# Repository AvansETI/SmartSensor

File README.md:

# SmartSensor
Author: _Maurice Snoeren (Lectoraat Smart Energy en Datascience & ICT)_

De SmartSensor is een resultaat van verschillende onderzoeken sinds 2018. Focus is gegeven aan laag vermogen, controle over energiestromen en eenvoud. Deze SmartSensor wordt binnen onderzoek en onderwijs toegepast.

## Inleiding
Meten is weten! Het belang van meten en het verzamelen van informatie is wel bekend. Echter komt het vaak  voor dat data niet voorhanden is of dat de data van beschikbare systemen van onvoldoende kwaliteit is. Bestaande meetsystemen zijn vaak kostbaar en onvoldoende flexibel om de benodigde aanpassingen te maken die nodig zijn binnen de verschillende onderzoeken. De SmartSensor biedt een open platform, waarmee eenvoudig vele meetpunten in een omgeving geïnstalleerd kunnen worden. Het platform biedt de mogelijkheid eigen metingen toe te voegen. Uniek is dat het met de SmartSensor mogelijk wordt om met andere systemen te communiceren. Hierdoor wordt het mogelijk om tevens sturing aan te brengen. Een open platform dat binnen Avans Hogeschool wordt ingezet voor het onderzoek en onderwijs.

## SmartSensor specificatie
- Atmega324PB (Microcontroller)
- ATECC608B (Trusted Platform Module)
- Zigbee module (of nRF24L01)
- Real-time klok
- Omgevingslichtsensor (0lx t/m 167klx, 5mlx res.) 
- Temperatuursensor (±0.5˚C, -40 t/m 100˚C)
- Luchtvochtigheidssensor (±4.5 %RH)
- CO2 sensor (optional, eCO2, 400 t/m 8192ppm) 
- Interfaces: RS232 (3.3V), I2C en SPI
- Uitbreiden met header

## Werking
Alle SmartSensoren staan met elkaar in verbinding door middel van een Zigbee mesh-netwerk. Eén van de sensoren dient als een coördinator te dienen om de meet¬gegevens uit het systeem te krijgen. Via deze coördinator kunnen tevens commando’s naar de verschillende sensoren gestuurd worden om bijvoorbeeld een batterij op te laden of de verwarming in te stellen op 20 graden Celsius.

## Metingen bestaande gebouwen
Door op verschillende punten te meten, krijgt men inzicht in de energiehuishouding van het bestaande gebouw. In veel (oude) gebouwen zijn er geen of onvoldoende meetpunten aanwezig. Met behulp van de SmartSensor kunnen deze meetpunten eenvoudig worden toegevoegd. Doordat met gebouwsystemen communiceert kan worden, is het tevens mogelijk de gegevens van deze systemen te verzamelen en mee te nemen in de analyse.

## Verduurzaming gebouwen
Binnen gebouwen kan de SmartSensor meetpunten realiseren én communiceren met gebouwsystemen. Hierdoor wordt het mogelijk om een regelsysteem te realiseren waarbij het gebouw kan worden verduurzaamd. Gebouwsystemen worden dan aangestuurd op basis van verschillende metingen. Door de flexibiliteit van deze SmartSensor wordt het eenvoudig om verschillende strategieën en technieken te onderzoeken en ontdekken.

## Nieuwbouw
Nieuwe gebouwen worden vaak opgeleverd met veel sensoren en gebouwbeheersystemen. Meer meetpunten is vaak niet nodig. In dit geval is het mogelijk om de SmartSensor te gebruiken om het gebouw-beheersysteem te valideren. Door vele metingen aan te brengen krijgt men inzicht in de kwaliteit en effectiviteit van het bestaande systeem. Daarnaast is het mogelijk om met de SmartSensor eenvoudig extra meetpunten aan te brengen binnen het gebouw.

## Onderzoek
De SmartSensor speelt steeds meer een rol binnen de onderzoeken naar slimme duurzame energiesystemen, datascience vraagstukken en het zelfbewuste huis.

## Interesse
Interesse voor samenwerking? Neem contact met ons op!

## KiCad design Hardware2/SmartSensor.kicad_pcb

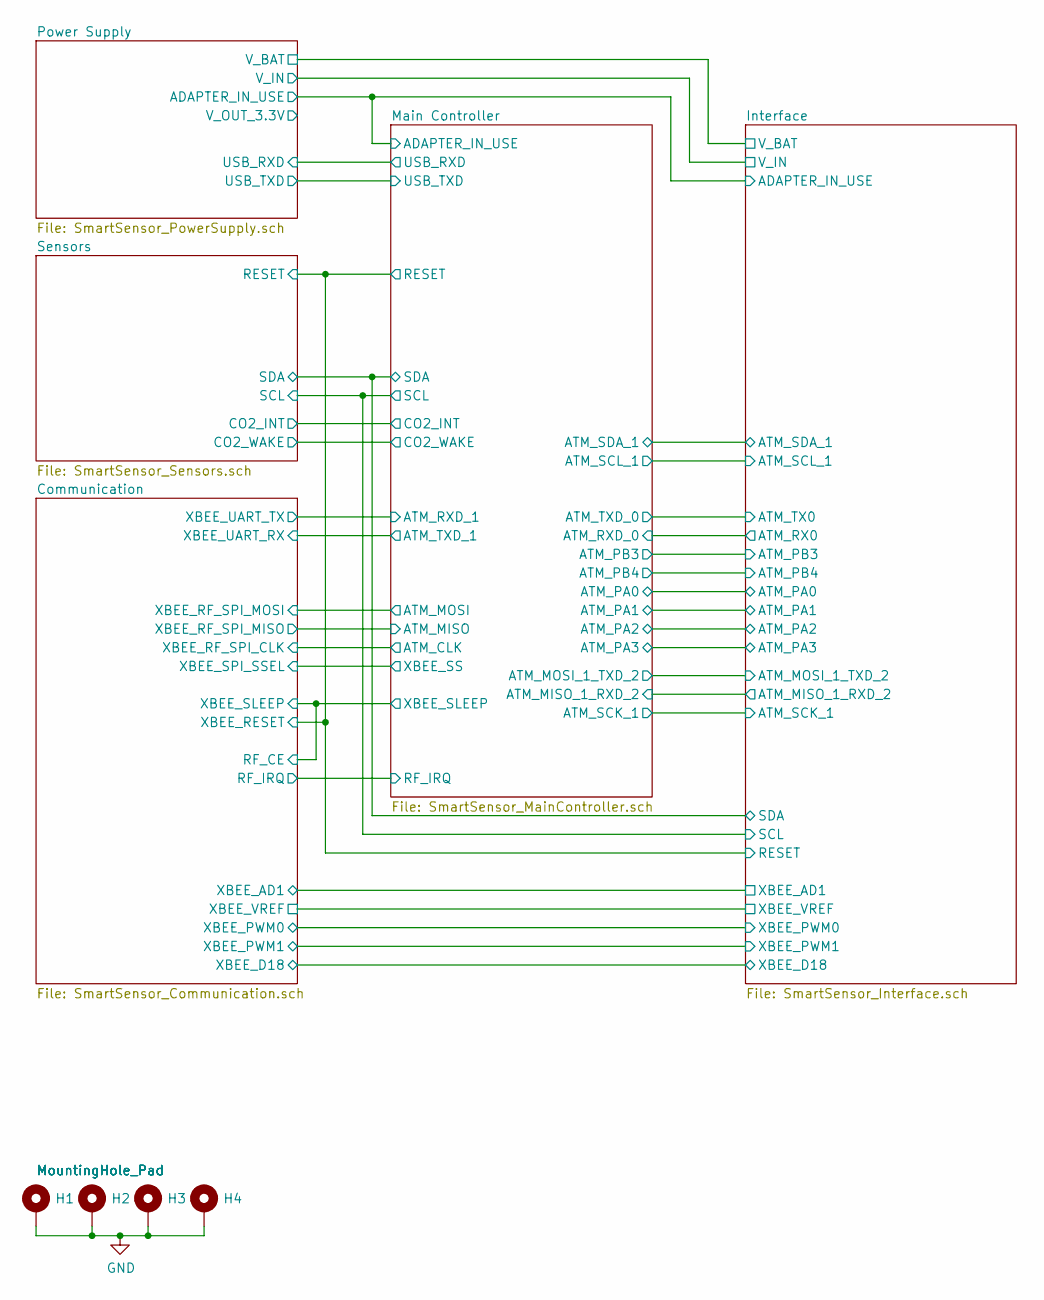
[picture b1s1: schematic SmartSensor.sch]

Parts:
H1, H2, H3, H4: MountingHole_Pad; MountingHole_2.2mm_M2_Pad_Via

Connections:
GND: H1.1, H2.1, H3.1, H4.1; also elsewhere on the board

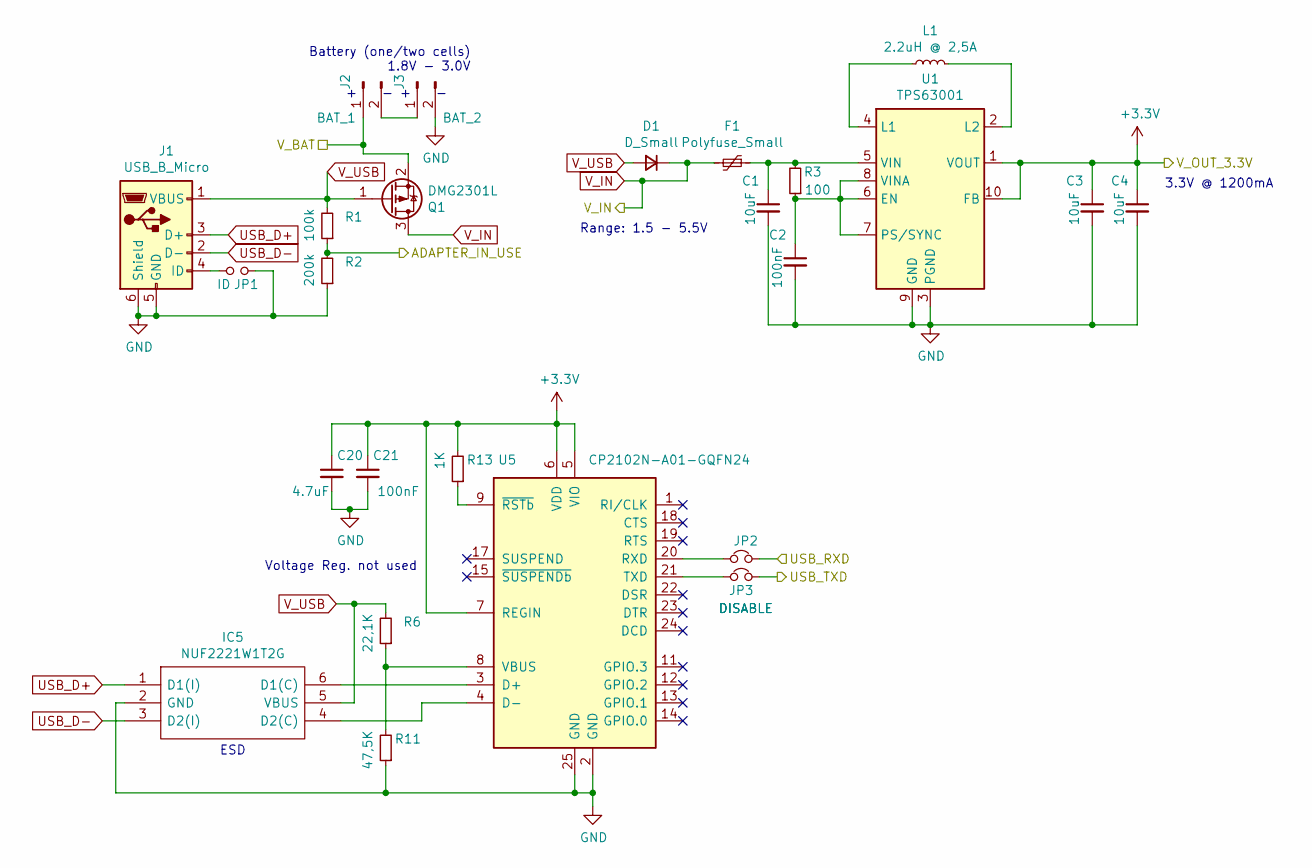
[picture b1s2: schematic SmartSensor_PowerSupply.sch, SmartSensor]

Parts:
C1, C3, C4: 10uF; C_0805_2012Metric
C2, C21: 100nF; C_0805_2012Metric
C20: 4.7uF; C_0805_2012Metric
D1: D_Small; D_0805_2012Metric
F1: Polyfuse_Small; Fuse_1812_4532Metric
IC5: NUF2221W1T2G; SOT65P210X110-6N; Mouser Part Number 863-NUF2221W1T2G
J1: USB_B_Micro; USB_Micro-B_Amphenol_10103594-0001LF_Horizontal
J2: BAT_1; PinHeader_1x02_P2.54mm_Vertical
J3: BAT_2; PinHeader_1x02_P2.54mm_Vertical
JP1: ID; SolderJumper-2_P1.3mm_Open_Pad1.0x1.5mm
JP2, JP3: DISABLE; SolderJumper-2_P1.3mm_Bridged2Bar_Pad1.0x1.5mm
L1: 2.2uH @ 2,5A; L_Vishay_IHLP-2020
Q1: DMG2301L; SOT-23
R1: 100k; R_0805_2012Metric
R2: 200k; R_0805_2012Metric
R3: 100; R_0805_2012Metric
R6: 22,1K; R_0805_2012Metric
R11: 47,5K; R_0805_2012Metric
R13: 1K; R_0805_2012Metric
U1: TPS63001; Texas_DRC0010J_ThermalVias
U5: CP2102N-A01-GQFN24; QFN-24-1EP_4x4mm_P0.5mm_EP2.6x2.6mm

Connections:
+3V3: C3.1, C4.1, C20.1, C21.1, R13.2, U1.1 (VOUT), U1.10 (FB), U5.5 (VIO), U5.6 (VDD), U5.7 (REGIN); also elsewhere on the board
/Interface/ADAPTER_IN_USE: R1.1, R2.2; also elsewhere on the board
/Interface/V_BAT: J2.1, Q1.2 (S); also elsewhere on the board
ATM_RXD_0: JP3.2; also elsewhere on the board
ATM_TXD_0: JP2.2; also elsewhere on the board
GND: C1.2, C2.2, C3.2, C4.2, C20.2, C21.2, IC5.2 (GND), J1.5 (GND), J1.6 (Shield), J3.2, JP1.2, R2.1, R11.1, U1.3 (PGND), U1.9 (GND), U1.11 (PGND), U5.2 (GND), U5.25 (GND); also elsewhere on the board
unnamed: C1.1, F1.1, R3.2, U1.5 (VIN)
unnamed: C2.1, R3.1, U1.6 (EN), U1.7 (PS/SYNC), U1.8 (VINA)
unnamed: IC5.4 (D2(C)), U5.4 (D-)
unnamed: IC5.6 (D1(C)), U5.3 (D+)
unnamed: J1.4 (ID), JP1.1
unnamed: J2.2, J3.1
unnamed: JP2.1, U5.20 (RXD)
unnamed: JP3.1, U5.21 (TXD)
unnamed: L1.1, U1.4 (L1)
unnamed: L1.2, U1.2 (L2)
unnamed: R6.1, R11.2, U5.8 (VBUS)
unnamed: R13.1, U5.9 (~RSTb)
USB_D+: IC5.1 (D1(I)), J1.3 (D+)
USB_D-: IC5.3 (D2(I)), J1.2 (D-)
V_IN: D1.1 (K), F1.2, Q1.3 (D); also elsewhere on the board
V_USB: D1.2 (A), IC5.5 (VBUS), J1.1 (VBUS), Q1.1 (G), R1.2, R6.2

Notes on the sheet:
Battery (one/two cells) 1.8V - 3.0V
3.3V @ 1200mA
Range: 1.5 - 5.5V
ESD
Voltage Reg. not used

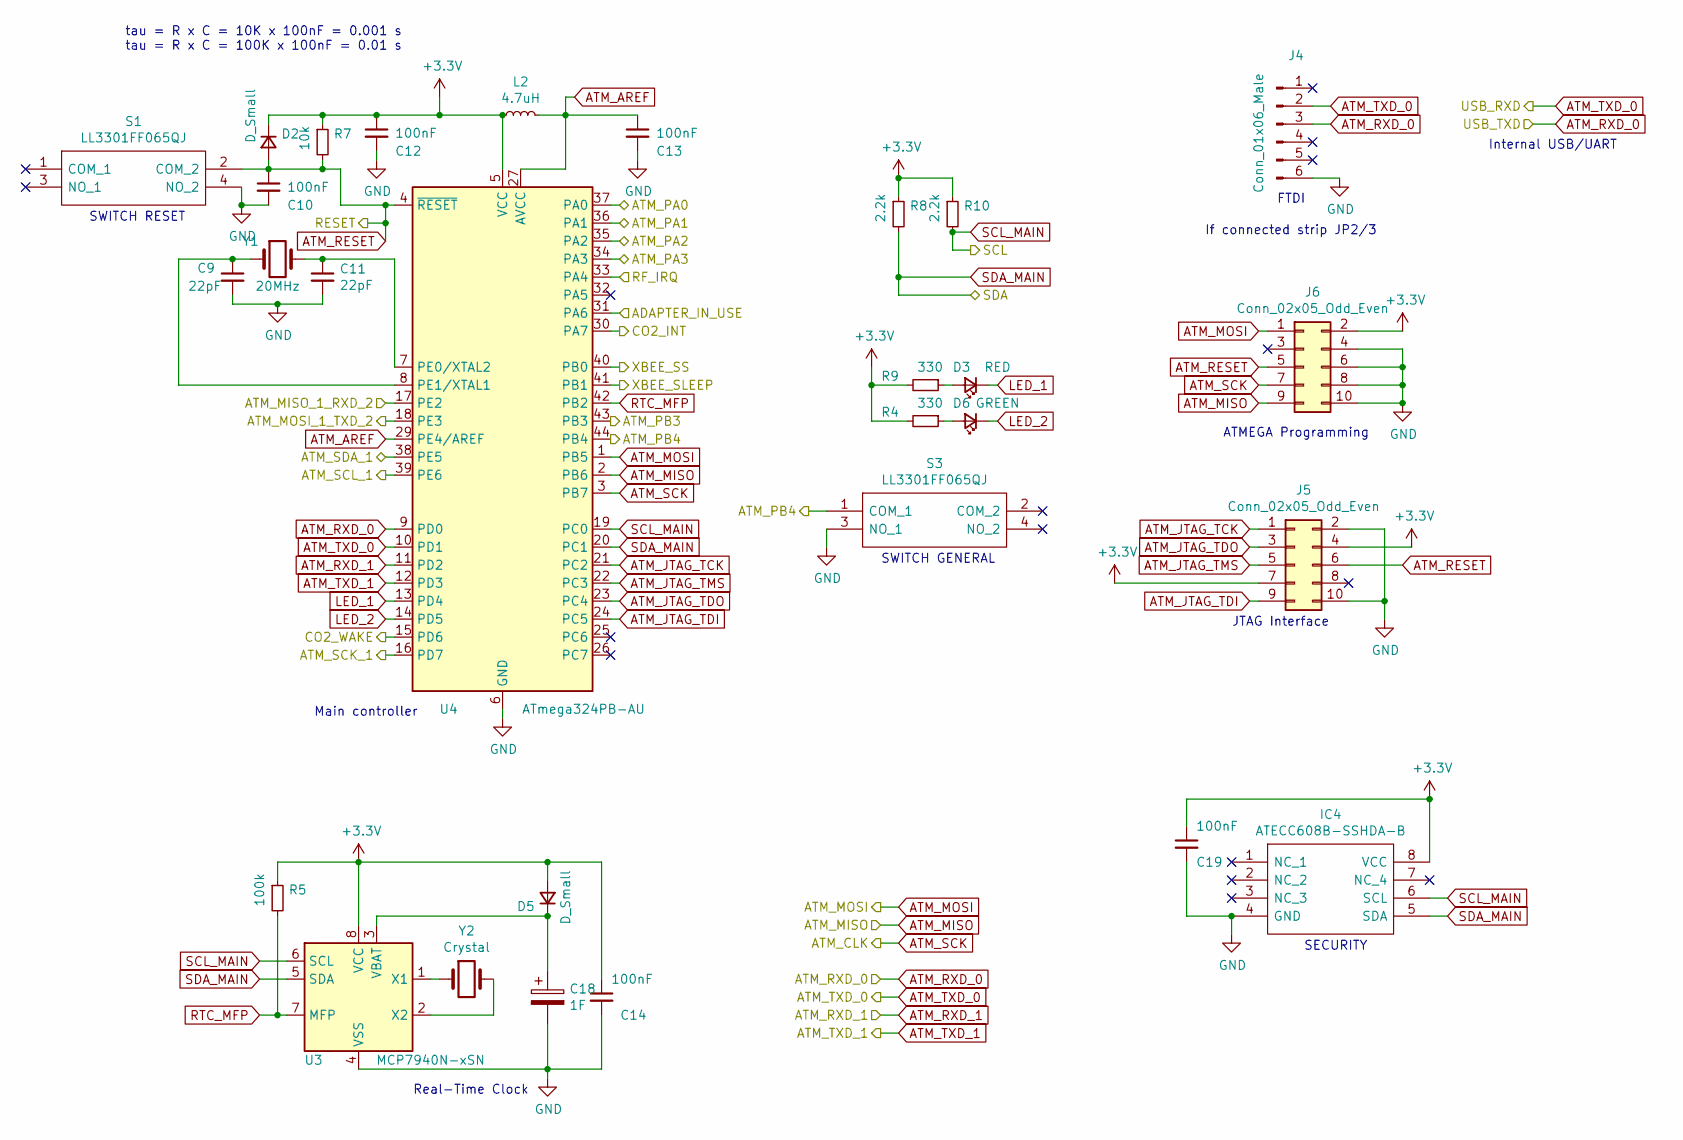
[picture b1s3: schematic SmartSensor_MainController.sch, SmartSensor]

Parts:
C9, C11: 22pF; C_0805_2012Metric
C10, C12, C13, C14, C19: 100nF; C_0805_2012Metric
C18: 1F; CP_Radial_D14.0mm_P5.00mm
D2, D5: D_Small; D_0805_2012Metric
D3: RED; LED_0805_2012Metric
D6: GREEN; LED_0805_2012Metric
IC4: ATECC608B-SSHDA-B; SOIC127P600X175-8N; Mouser Part Number 579-TECC608B-SSHDA-B
J4: Conn_01x06_Male; PinHeader_1x06_P2.54mm_Vertical
J5, J6: Conn_02x05_Odd_Even; PinHeader_2x05_P2.54mm_Vertical
L2: 4.7uH; L_1206_3216Metric_Pad1.42x1.75mm_HandSolder
R4, R9: 330; R_0805_2012Metric
R5: 100k; R_0805_2012Metric
R7: 10k; R_0805_2012Metric
R8, R10: 2.2k; R_0805_2012Metric
S1, S3: LL3301FF065QJ; Mouser Part Number 612-LL3301FF065QJ
U3: MCP7940N-xSN; SOIC-8_3.9x4.9mm_P1.27mm
U4: ATmega324PB-AU; TQFP-44_10x10mm_P0.8mm
Y1: 20MHz; Crystal_SMD_Abracon_ABM3-2Pin_5.0x3.2mm
Y2: Crystal; Crystal_SMD_G8-2Pin_3.2x1.5mm

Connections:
+3V3: C12.1, C14.1, C19.1, D2.1 (K), D5.2 (A), IC4.8 (VCC), J5.4, J5.7, J6.2, L2.1, R4.2, R5.1, R7.1, R8.1, R9.2, R10.1, U3.8 (VCC), U4.5 (VCC); also elsewhere on the board
/Communication/RF_IRQ: U4.33 (PA4); also elsewhere on the board
/Interface/ADAPTER_IN_USE: U4.31 (PA6); also elsewhere on the board
/Interface/ATM_MISO_1_RXD_2: U4.17 (PE2); also elsewhere on the board
/Interface/ATM_MOSI_1_TXD_2: U4.18 (PE3); also elsewhere on the board
/Interface/ATM_PA0: U4.37 (PA0); also elsewhere on the board
/Interface/ATM_PA1: U4.36 (PA1); also elsewhere on the board
/Interface/ATM_PA2: U4.35 (PA2); also elsewhere on the board
/Interface/ATM_PA3: U4.34 (PA3); also elsewhere on the board
/Interface/ATM_PB3: U4.43 (PB3); also elsewhere on the board
/Interface/ATM_PB4: S3.1 (COM_1), U4.44 (PB4); also elsewhere on the board
/Interface/ATM_SCK_1: U4.16 (PD7); also elsewhere on the board
/Interface/ATM_SCL_1: U4.39 (PE6); also elsewhere on the board
/Interface/ATM_SDA_1: U4.38 (PE5); also elsewhere on the board
ATM_AREF: C13.1, L2.2, U4.27 (AVCC), U4.29 (PE4/AREF)
ATM_JTAG_TCK: J5.1, U4.21 (PC2)
ATM_JTAG_TDI: J5.9, U4.24 (PC5)
ATM_JTAG_TDO: J5.3, U4.23 (PC4)
ATM_JTAG_TMS: J5.5, U4.22 (PC3)
ATM_MISO: J6.9, U4.2 (PB6); also elsewhere on the board
ATM_MOSI: J6.1, U4.1 (PB5); also elsewhere on the board
ATM_RESET: C10.1, D2.2 (A), J5.6, J6.5, R7.2, S1.2 (COM_2), U4.4 (~RESET); also elsewhere on the board
ATM_RXD_0: J4.3, U4.9 (PD0); also elsewhere on the board
ATM_RXD_1: U4.11 (PD2); also elsewhere on the board
ATM_SCK: J6.7, U4.3 (PB7); also elsewhere on the board
ATM_TXD_0: J4.2, U4.10 (PD1); also elsewhere on the board
ATM_TXD_1: U4.12 (PD3); also elsewhere on the board
CO2_INT: U4.30 (PA7); also elsewhere on the board
CO2_WAKE: U4.15 (PD6); also elsewhere on the board
GND: C9.2, C10.2, C11.2, C12.2, C13.2, C14.2, C18.2, C19.2, IC4.4 (GND), J4.6, J5.2, J5.10, J6.4, J6.6, J6.8, J6.10, S1.4 (NO_2), S3.3 (NO_1), U3.4 (VSS), U4.6 (GND), U4.28 (GND); also elsewhere on the board
LED_1: D3.1 (K), U4.13 (PD4)
LED_2: D6.1 (K), U4.14 (PD5)
unnamed: C9.1, U4.8 (PE1/XTAL1), Y1.1
unnamed: C11.1, U4.7 (PE0/XTAL2), Y1.2
unnamed: C18.1, D5.1 (K), U3.3 (VBAT)
unnamed: D3.2 (A), R9.1
unnamed: D6.2 (A), R4.1
unnamed: U3.1 (X1), Y2.1
unnamed: U3.2 (X2), Y2.2
RTC_MFP: R5.2, U3.7 (MFP), U4.42 (PB2)
SCL: IC4.6 (SCL), R10.2, U3.6 (SCL), U4.19 (PC0); also elsewhere on the board
SDA: IC4.5 (SDA), R8.2, U3.5 (SDA), U4.20 (PC1); also elsewhere on the board
XBEE_SLEEP: U4.41 (PB1); also elsewhere on the board
XBEE_SPI_SSEL: U4.40 (PB0); also elsewhere on the board

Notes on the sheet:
JTAG Interface
Real-Time Clock
ATMEGA Programming
FTDI
SECURITY
tau = R x C = 10K x 100nF = 0.001 s tau = R x C = 100K x 100nF = 0.01 s
Main controller
SWITCH RESET
SWITCH GENERAL
Internal USB/UART
If connected strip JP2/3

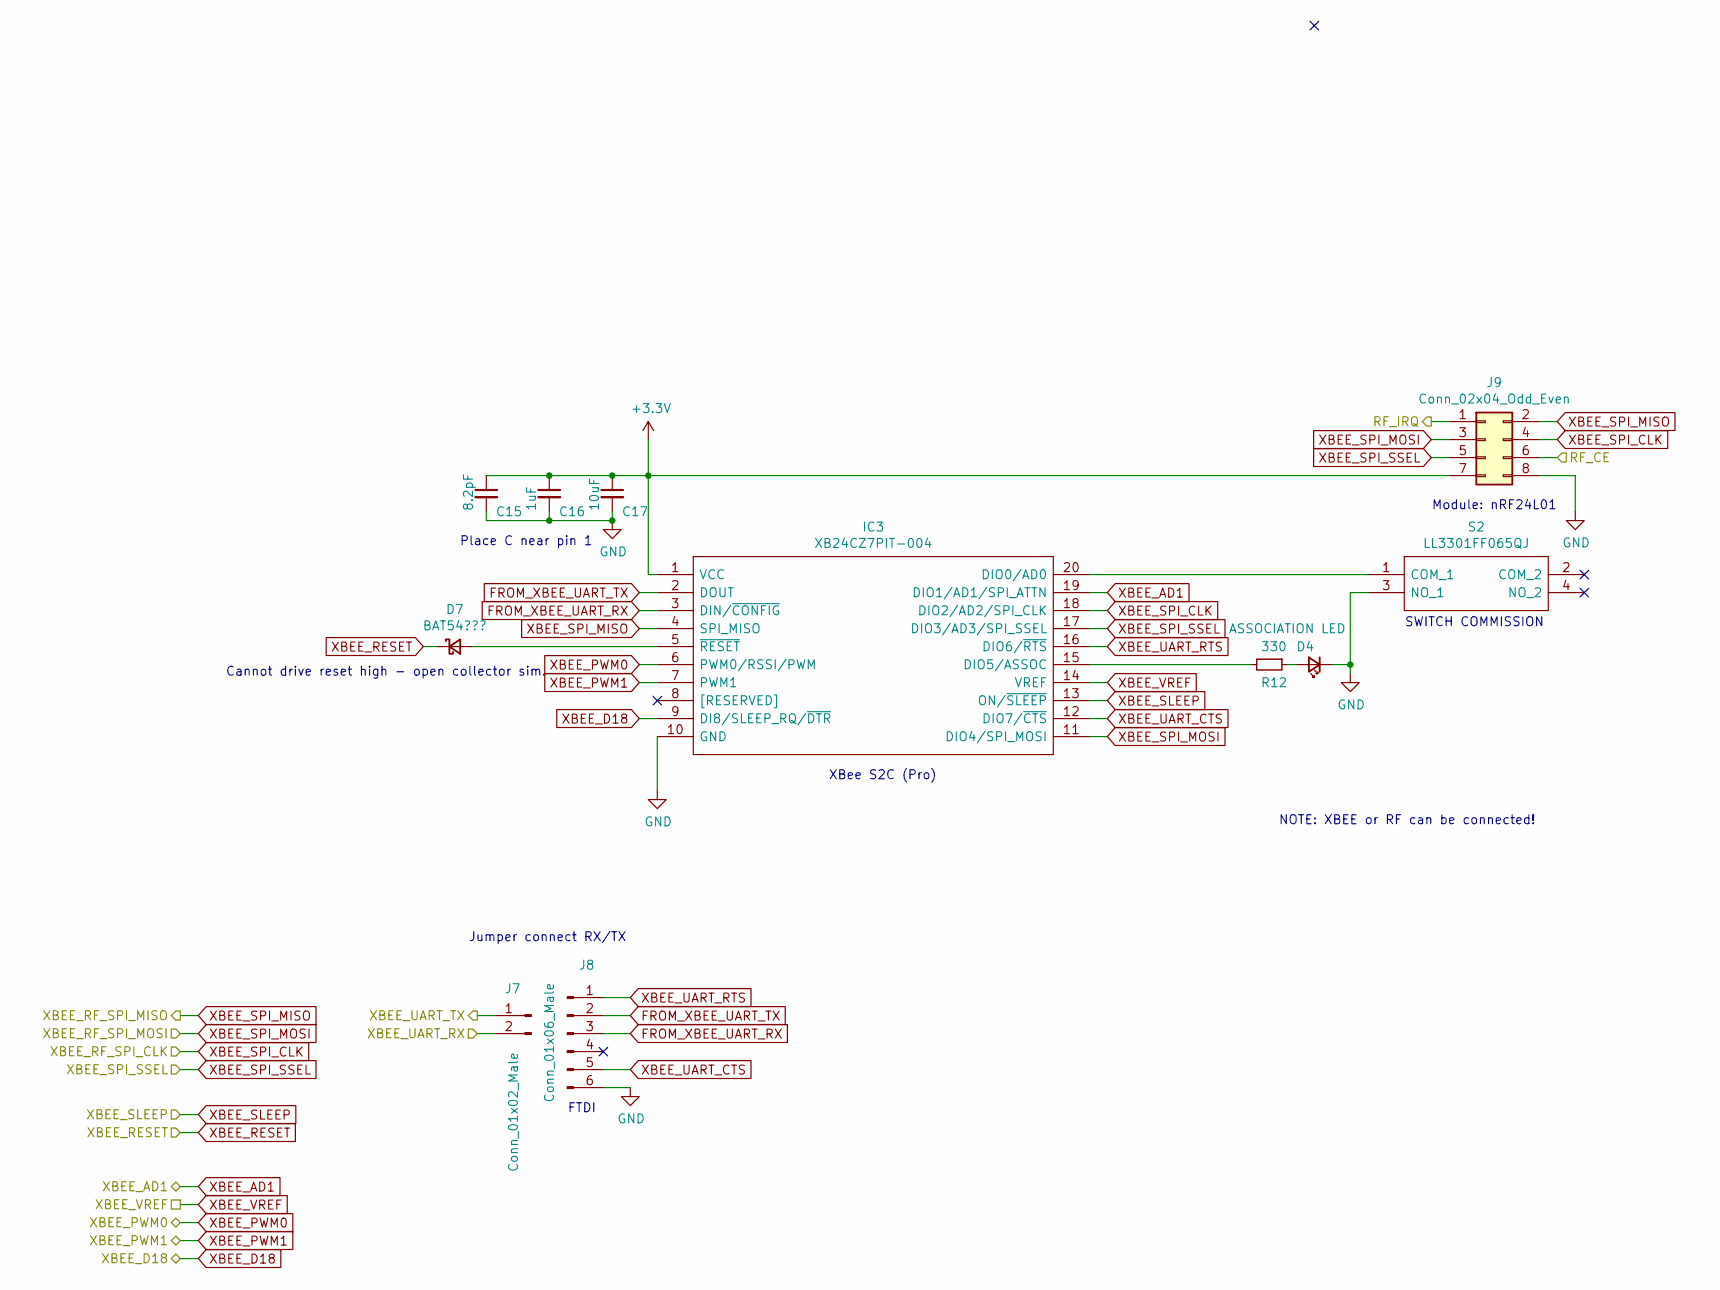
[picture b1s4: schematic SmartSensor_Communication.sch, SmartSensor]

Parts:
C15: 8.2pF; C_0805_2012Metric
C16: 1uF; C_0805_2012Metric
C17: 10uF; C_0805_2012Metric
D4: ASSOCIATION LED; LED_0805_2012Metric
D7: BAT54???; D_0805_2012Metric
IC3: XB24CZ7PIT-004; XB24CAPIT-001; Manufacturer_Part_Number XB24CZ7PIT-004; Mouser Part Number 888-XB24CZ7PIT-004
J7: Conn_01x02_Male; PinHeader_1x02_P2.54mm_Vertical
J8: Conn_01x06_Male; PinHeader_1x06_P2.54mm_Vertical
J9: Conn_02x04_Odd_Even; PinHeader_2x04_P2.54mm_Vertical
R12: 330; R_0805_2012Metric
S2: LL3301FF065QJ; Mouser Part Number 612-LL3301FF065QJ

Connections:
+3V3: C15.1, C16.1, C17.1, IC3.1 (VCC), J9.7; also elsewhere on the board
/Communication/RF_IRQ: J9.1; also elsewhere on the board
ATM_MISO: IC3.4 (SPI_MISO), J9.2; also elsewhere on the board
ATM_MOSI: IC3.11 (DIO4/SPI_MOSI), J9.3; also elsewhere on the board
ATM_RESET: D7.1 (K); also elsewhere on the board
ATM_RXD_1: J7.1; also elsewhere on the board
ATM_SCK: IC3.18 (DIO2/AD2/SPI_CLK), J9.4; also elsewhere on the board
ATM_TXD_1: J7.2; also elsewhere on the board
FROM_XBEE_UART_RX: IC3.3 (DIN/~CONFIG), J8.3
FROM_XBEE_UART_TX: IC3.2 (DOUT), J8.2
GND: C15.2, C16.2, C17.2, D4.1 (K), IC3.10 (GND), J8.6, J9.8, S2.3 (NO_1); also elsewhere on the board
unnamed: D4.2 (A), R12.1
unnamed: D7.2 (A), IC3.5 (~RESET)
unnamed: IC3.15 (DIO5/ASSOC), R12.2
unnamed: IC3.20 (DIO0/AD0), S2.1 (COM_1)
XBEE_AD1: IC3.19 (DIO1/AD1/SPI_ATTN); also elsewhere on the board
XBEE_D18: IC3.9 (DI8/SLEEP_RQ/~DTR); also elsewhere on the board
XBEE_PWM0: IC3.6 (PWM0/RSSI/PWM); also elsewhere on the board
XBEE_PWM1: IC3.7 (PWM1); also elsewhere on the board
XBEE_SLEEP: IC3.13 (ON/~SLEEP), J9.6; also elsewhere on the board
XBEE_SPI_SSEL: IC3.17 (DIO3/AD3/SPI_SSEL), J9.5; also elsewhere on the board
XBEE_UART_CTS: IC3.12 (DIO7/~CTS), J8.5
XBEE_UART_RTS: IC3.16 (DIO6/~RTS), J8.1
XBEE_VREF: IC3.14 (VREF); also elsewhere on the board

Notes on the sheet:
Place C near pin 1
XBee S2C (Pro)
Module: nRF24L01
NOTE: XBEE or RF can be connected!
Jumper connect RX/TX
FTDI
SWITCH COMMISSION
Cannot drive reset high - open collector sim.

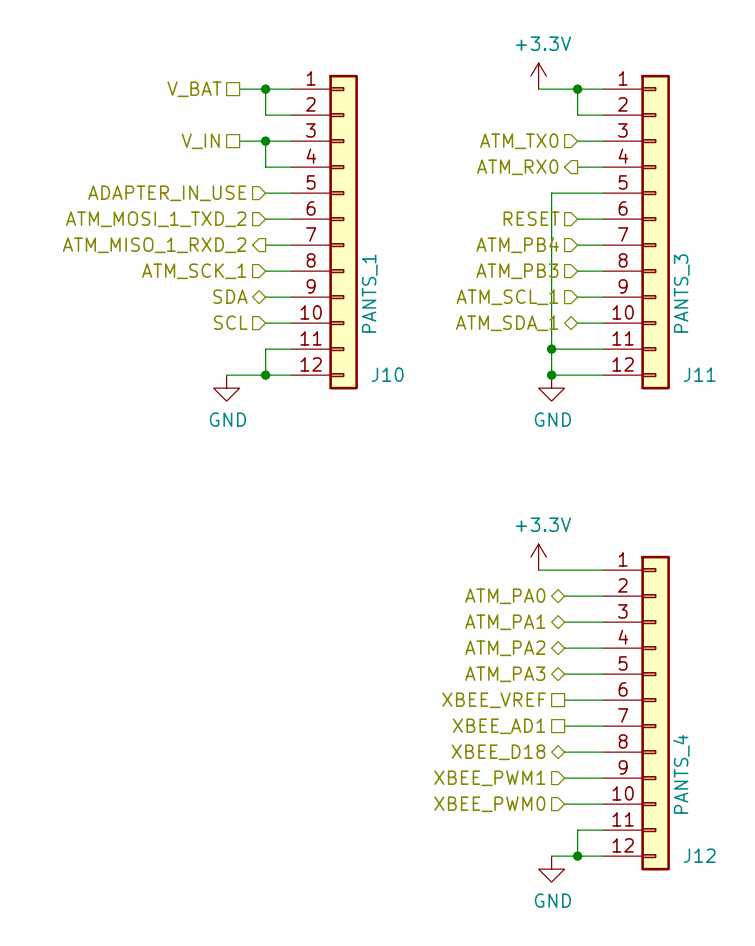
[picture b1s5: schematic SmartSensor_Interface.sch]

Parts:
J10: PANTS_1; PinHeader_1x12_P2.54mm_Vertical
J11: PANTS_3; PinHeader_1x12_P2.54mm_Vertical
J12: PANTS_4; PinHeader_1x12_P2.54mm_Vertical

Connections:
+3V3: J11.1, J11.2, J12.1; also elsewhere on the board
/Interface/ADAPTER_IN_USE: J10.5; also elsewhere on the board
/Interface/ATM_MISO_1_RXD_2: J10.7; also elsewhere on the board
/Interface/ATM_MOSI_1_TXD_2: J10.6; also elsewhere on the board
/Interface/ATM_PA0: J12.2; also elsewhere on the board
/Interface/ATM_PA1: J12.3; also elsewhere on the board
/Interface/ATM_PA2: J12.4; also elsewhere on the board
/Interface/ATM_PA3: J12.5; also elsewhere on the board
/Interface/ATM_PB3: J11.8; also elsewhere on the board
/Interface/ATM_PB4: J11.7; also elsewhere on the board
/Interface/ATM_SCK_1: J10.8; also elsewhere on the board
/Interface/ATM_SCL_1: J11.9; also elsewhere on the board
/Interface/ATM_SDA_1: J11.10; also elsewhere on the board
/Interface/V_BAT: J10.1, J10.2; also elsewhere on the board
ATM_RESET: J11.6; also elsewhere on the board
ATM_RXD_0: J11.4; also elsewhere on the board
ATM_TXD_0: J11.3; also elsewhere on the board
GND: J10.11, J10.12, J11.5, J11.11, J11.12, J12.11, J12.12; also elsewhere on the board
SCL: J10.10; also elsewhere on the board
SDA: J10.9; also elsewhere on the board
V_IN: J10.3, J10.4; also elsewhere on the board
XBEE_AD1: J12.7; also elsewhere on the board
XBEE_D18: J12.8; also elsewhere on the board
XBEE_PWM0: J12.10; also elsewhere on the board
XBEE_PWM1: J12.9; also elsewhere on the board
XBEE_VREF: J12.6; also elsewhere on the board

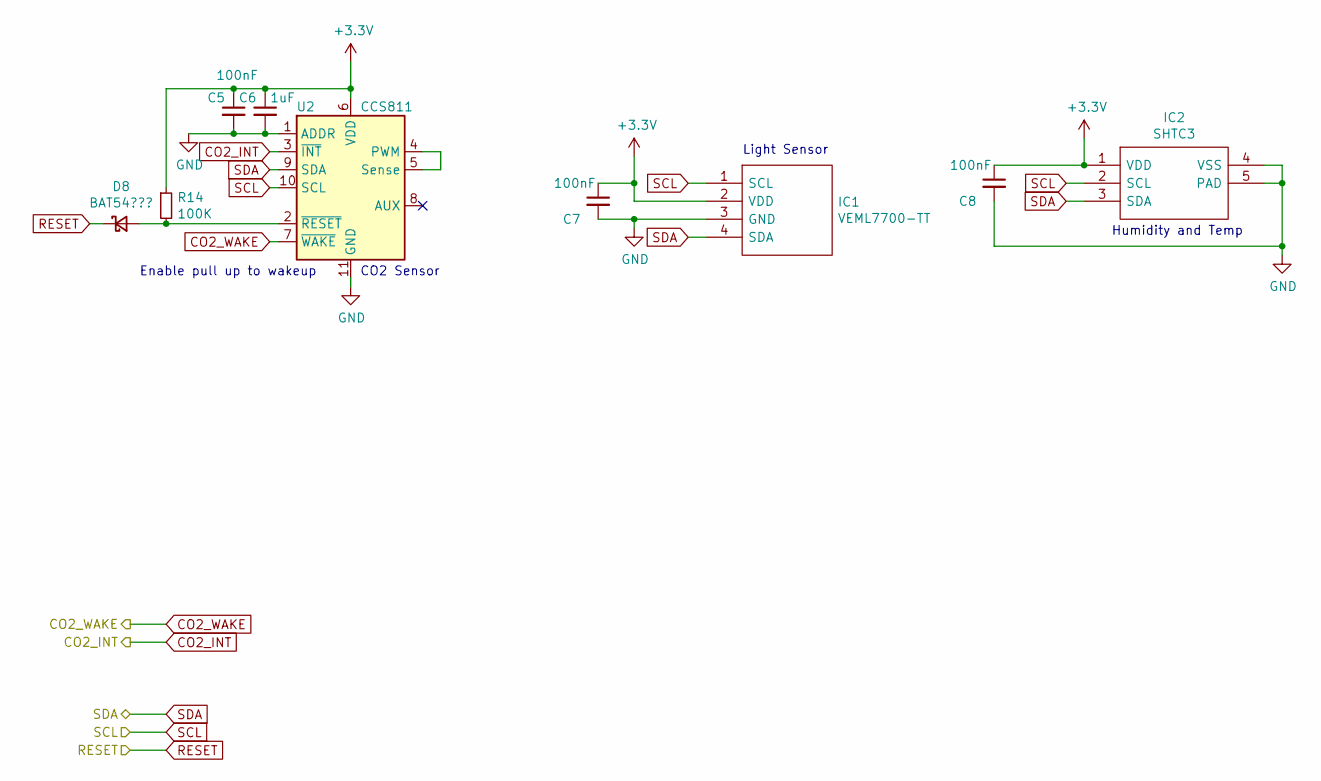
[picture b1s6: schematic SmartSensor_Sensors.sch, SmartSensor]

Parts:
C5, C7, C8: 100nF; C_0805_2012Metric
C6: 1uF; C_0805_2012Metric
D8: BAT54???; D_0805_2012Metric
IC1: VEML7700-TT; VEML7700; Mouser Part Number 78-VEML7700-TT
IC2: SHTC3; AMS_QFN-4-1EP_2x2mm_P0.95mm_EP0.7x1.6mm; Manufacturer_Part_Number SHTC3; Mouser Part Number 403-SHTC3
R14: 100K; R_0805_2012Metric
U2: CCS811; AMS_LGA-10-1EP_2.7x4mm_P0.6mm

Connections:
+3V3: C5.1, C6.1, C7.1, C8.1, IC1.2 (VDD), IC2.1 (VDD), R14.1, U2.6 (VDD); also elsewhere on the board
ATM_RESET: D8.1 (K); also elsewhere on the board
CO2_INT: U2.3 (~INT); also elsewhere on the board
CO2_WAKE: U2.7 (~WAKE); also elsewhere on the board
GND: C5.2, C6.2, C7.2, C8.2, IC1.3 (GND), IC2.4 (VSS), IC2.5 (PAD), U2.1 (ADDR), U2.11 (GND); also elsewhere on the board
unnamed: D8.2 (A), R14.2, U2.2 (~RESET)
unnamed: U2.4 (PWM), U2.5 (Sense)
SCL: IC1.1 (SCL), IC2.2 (SCL), U2.10 (SCL); also elsewhere on the board
SDA: IC1.4 (SDA), IC2.3 (SDA), U2.9 (SDA); also elsewhere on the board

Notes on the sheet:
CO2 Sensor
Light Sensor
Humidity and Temp
Enable pull up to wakeup

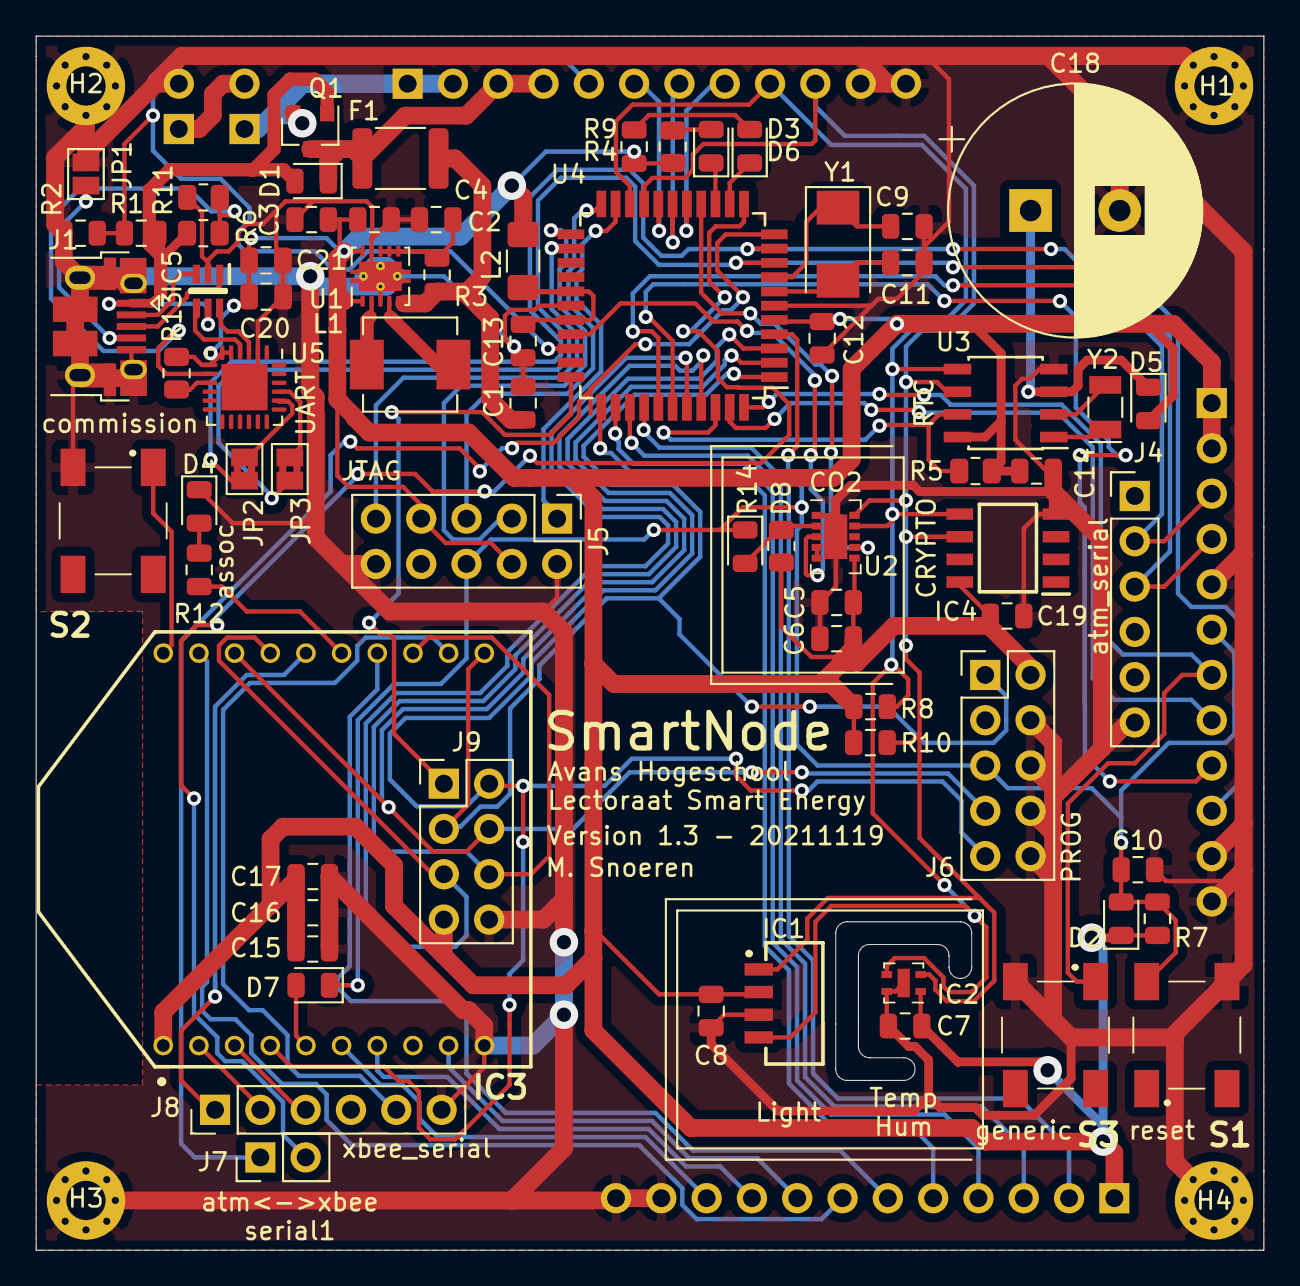
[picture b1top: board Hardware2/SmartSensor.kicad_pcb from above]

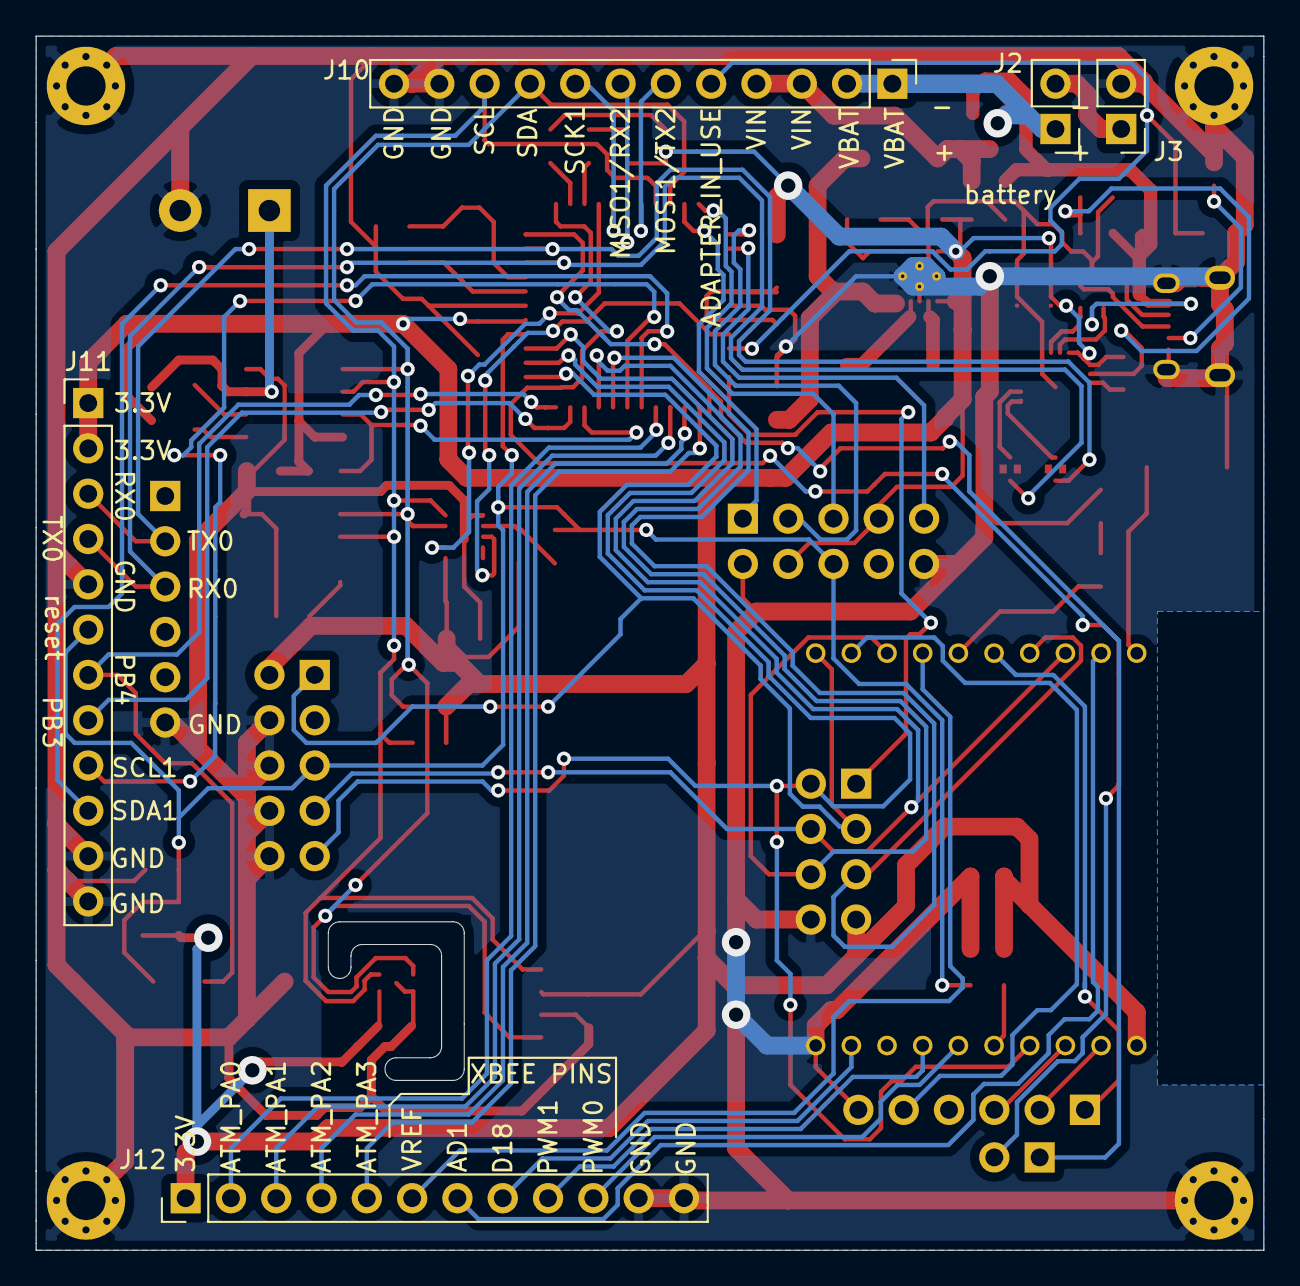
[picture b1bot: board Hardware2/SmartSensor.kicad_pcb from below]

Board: 2 copper layers, 68.8 x 68.1 mm, 81 parts (5 on the bottom side), 76 nets.

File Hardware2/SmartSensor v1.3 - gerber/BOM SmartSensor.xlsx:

Id | Designator | Package | Quantity | Designation | Mouser
1 | U4 | TQFP-44_10x10mm_P0.8mm | 1 | ATmega324PB-AU | ATMEGA324PB-AU
2 | IC5 | SOT65P210X110-6N | 1 | NUF2221W1T2G | NUF2221W1T2G
3 | R7 | R_0805_2012Metric | 1 | 10k
4 | C1,C3,C4,C17 | C_0805_2012Metric | 4 | 10uF
5 | C2,C5,C7,C8,C10,C12,C13,C14,C19,C21 | C_0805_2012Metric | 10 | 100nF
6 | C6,C16 | C_0805_2012Metric | 2 | 1uF
7 | C9,C11 | C_0805_2012Metric | 2 | 22pF
8 | C15 | C_0805_2012Metric | 1 | 8.2pF
9 | C18 | CP_Radial_D14.0mm_P5.00mm | 1 | 1F
10 | D1,D2,D5 | D_0805_2012Metric | 3 | D_Small | NSVR1020MW2T1G
11 | D3, D4 | LED_0805_2012Metric | 1 | RED | 150080SS75000
13 | F1 | Fuse_1812_4532Metric | 1 | Polyfuse_Small | 1812L300MR
14 | IC2 | AMS_QFN-4-1EP_2x2mm_P0.95mm_EP0.7x1.6mm | 1 | SHTC3 | SHTC3
15 | J1 | USB_Micro-B_Amphenol_10103594-0001LF_Horizontal | 1 | USB_B_Micro | 10103594-0001LF
16 | J2 | PinHeader_1x02_P2.54mm_Vertical | 1 | BAT_1
17 | J3 | PinHeader_1x02_P2.54mm_Vertical | 1 | BAT_2
18 | J4,J8 | PinHeader_1x06_P2.54mm_Vertical | 2 | Conn_01x06_Male
19 | J5,J6 | PinHeader_2x05_P2.54mm_Vertical | 2 | Conn_02x05_Odd_Even
20 | J7 | PinHeader_1x02_P2.54mm_Vertical | 1 | Conn_01x02_Male
21 | J9 | PinHeader_2x04_P2.54mm_Vertical | 1 | Conn_02x04_Odd_Even
22 | J10 | PinHeader_1x12_P2.54mm_Vertical | 1 | PANTS_1
23 | J11 | PinHeader_1x12_P2.54mm_Vertical | 1 | PANTS_3
24 | J12 | PinHeader_1x12_P2.54mm_Vertical | 1 | PANTS_4
25 | L1 | L_Vishay_IHLP-2020 | 1 | 2.2uH @ 2,5A | IHLP2020CZER2R2M11
26 | L2 | L_1206_3216Metric_Pad1.42x1.75mm_HandSolder | 1 | 4.7uH | AIML-1206-4R7K-T
27 | Q1 | SOT-23 | 1 | DMG2301L | DMG2301LK-7
28 | R1,R5 | R_0805_2012Metric | 2 | 100k
29 | R2 | R_0805_2012Metric | 1 | 200k
30 | R3 | R_0805_2012Metric | 1 | 100
31 | R8,R10 | R_0805_2012Metric | 2 | 2.2k
32 | R9,R12,R4 | R_0805_2012Metric | 3 | 330
33 | U1 | Texas_DRC0010J_ThermalVias | 1 | TPS63001 | TPS63001DRCR
34 | U2 | AMS_LGA-10-1EP_2.7x4mm_P0.6mm | 1 | CCS811 | CCS811B-JOPR
35 | U3 | SOIC-8_3.9x4.9mm_P1.27mm | 1 | MCP7940N-xSN | MCP7940N-I/SN
36 | Y2 | Crystal_SMD_G8-2Pin_3.2x1.5mm | 1 | Crystal | ABS07W-32.768kHz-K-1-T
37 | IC3 | XB24CAPIT-001 | 1 | XB24CZ7PIT-004 | XB24CAWIT-001
38 | IC4 | SOIC127P600X175-8N | 1 | ATECC608B-SSHDA-B | ATECC608B-SSHDA-B
39 | Y1 | Crystal_SMD_Abracon_ABM3-2Pin_5.0x3.2mm | 1 | 20MHz | ABM3AIG-20.000MHZ-8-1R-T
41 | IC1 | VEML7700 | 1 | VEML7700-TT | VEML7700-TT
42 | S1,S2,S3 | LL3301FF065QJ | 3 | LL3301FF065QJ | LL3301FF065QJ
43 | D6 | LED_0805_2012Metric | 1 | GREEN | 150080GS75000
44 | C20 | C_0805_2012Metric | 1 | 4.7uF | CL21A475KPFNNWE
45 | D7,D8 | D_0805_2012Metric | 2 | B360Q-13-F | https://nl.mouser.com/ProductDetail/Diodes-Incorporated/B360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
48 | R6 | R_0805_2012Metric | 1 | 22,1K
49 | R11 | R_0805_2012Metric | 1 | 47,5K
50 | R13 | R_0805_2012Metric | 1 | 1K
51 | R14 | R_0805_2012Metric | 1 | 100K
52 | U5 | QFN-24-1EP_4x4mm_P0.5mm_EP2.6x2.6mm | 1 | CP2102N-A01-GQFN24 | CP2102N-A02-GQFN24

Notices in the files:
README.md:
License: MIT
